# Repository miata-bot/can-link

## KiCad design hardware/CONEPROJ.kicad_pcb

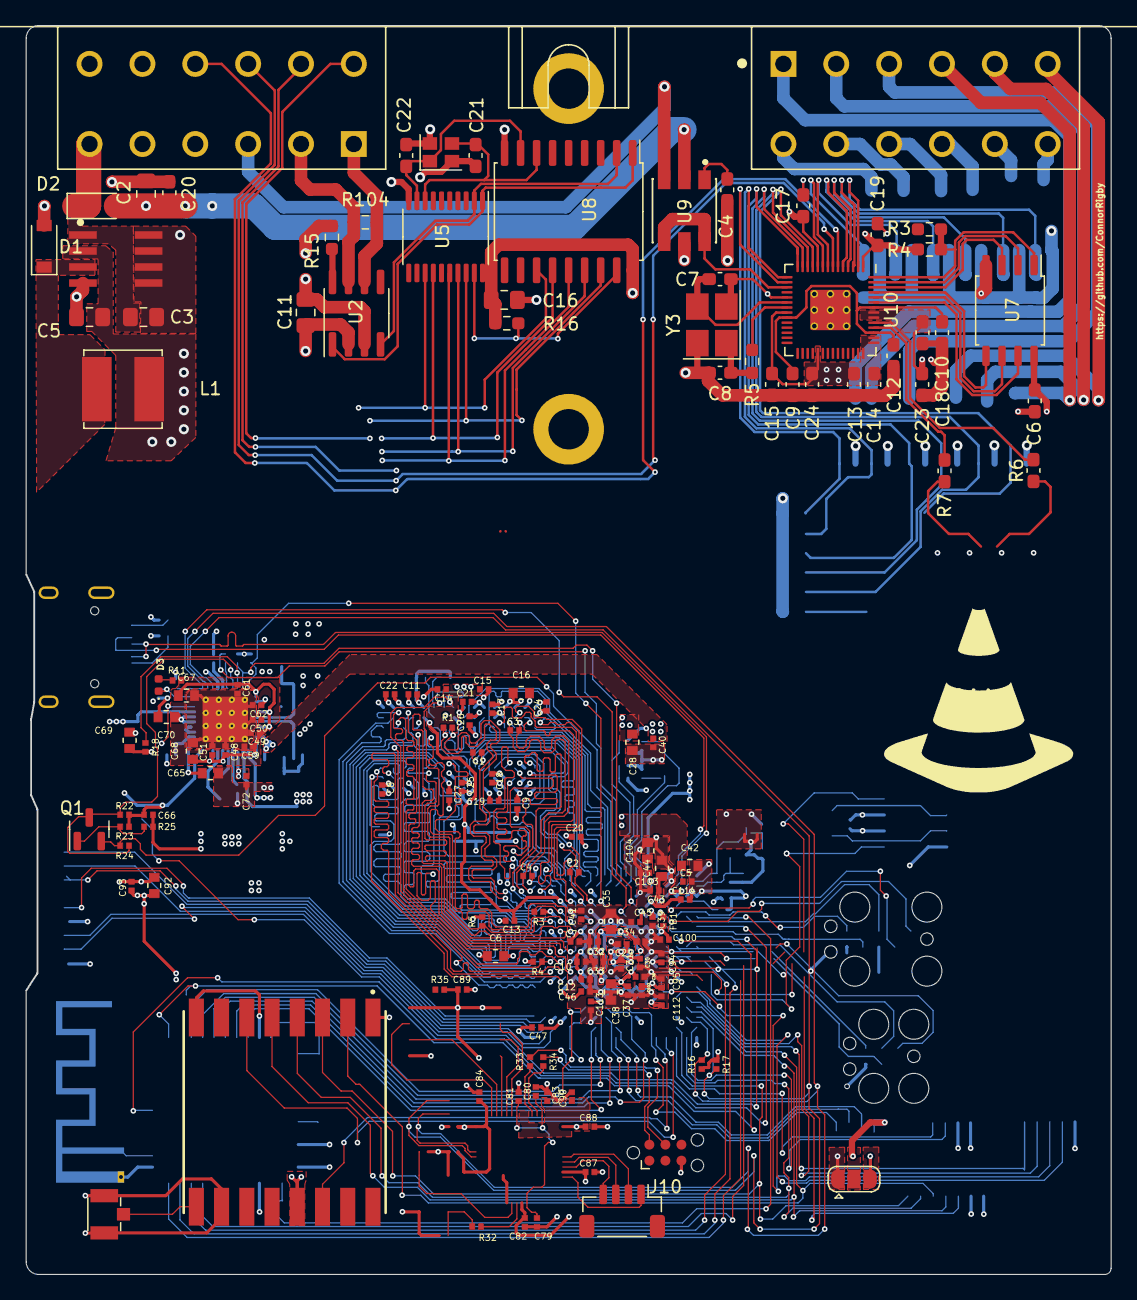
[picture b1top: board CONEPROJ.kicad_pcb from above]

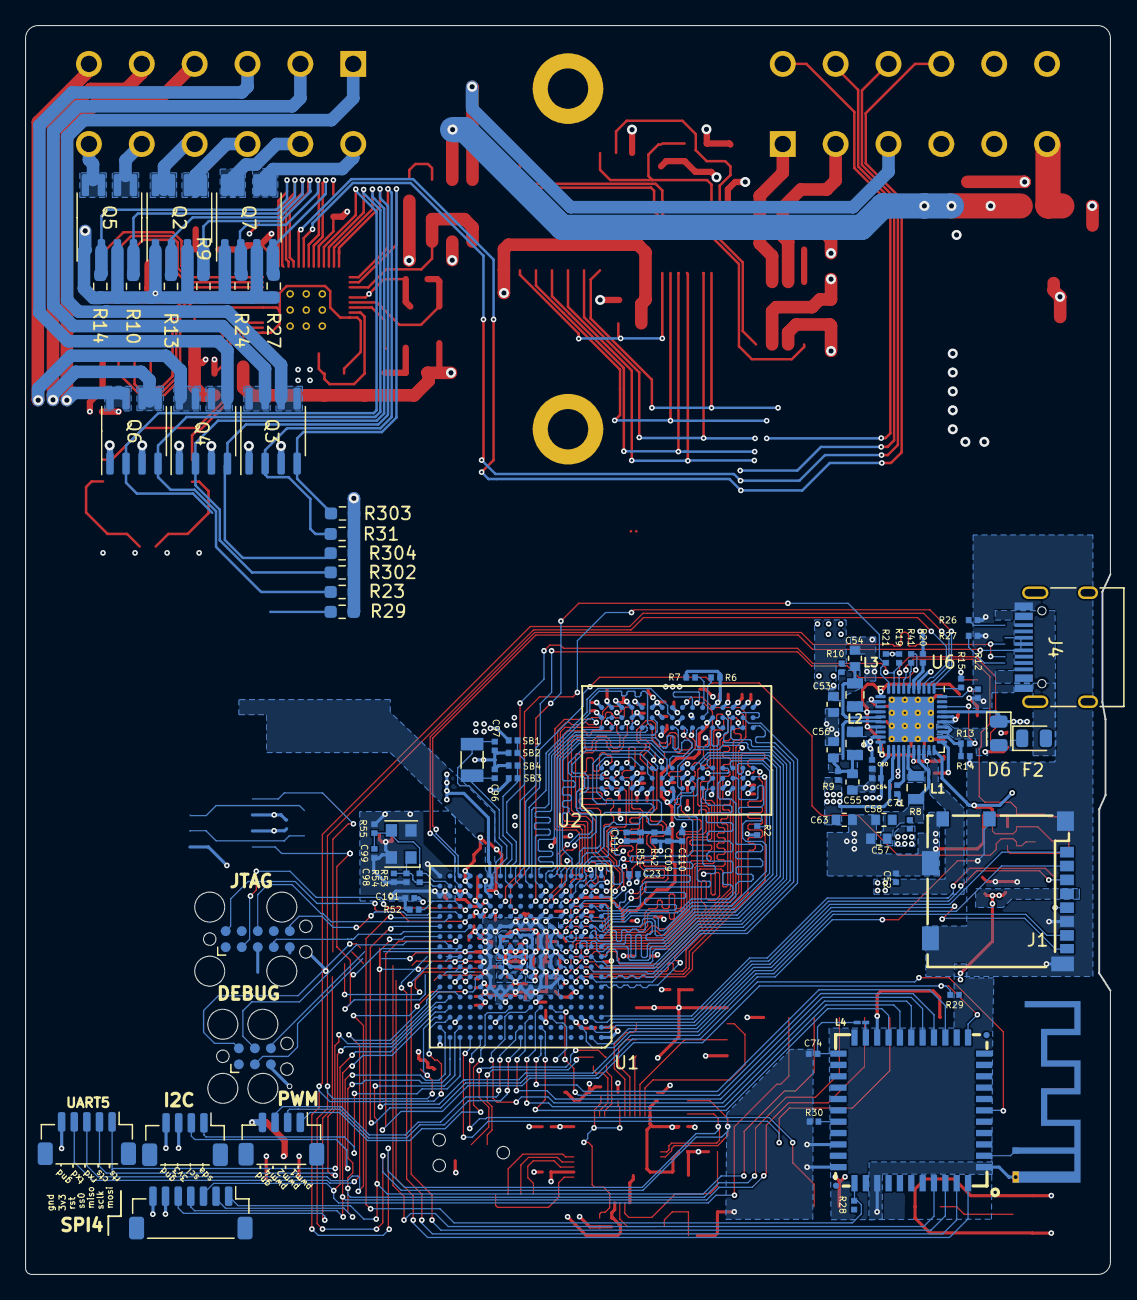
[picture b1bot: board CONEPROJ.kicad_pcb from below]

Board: 4 copper layers, 86.0 x 99.0 mm, 240 parts (89 on the bottom side), 60 nets.

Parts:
AE1: U.FL-R-SMT-1(10); HRS_U.FL-R-SMT-1(10)
ANT1: PCB_ANTENNA; Texas_SWRA117D_2.4GHz_Left
C1, C2#2, C3, C4#2: 2.2pF; C_0402_narrow
C2, C3#2, C5#2, C11, C16: 10uF; C_0805_2012Metric_Pad1.18x1.45mm_HandSolder
C4, C10, C13, C14, C15, C17#2, C18, C19#2, C20#2, C23, C24#2: 0.1uF; C_0603_1608Metric_Pad1.08x0.95mm_HandSolder
C5, C7#2, C8#2, C9#2, C10#2, C11#2, C12, C13#2, C14#2, C15#2, C17, C18#2, C19, C20, C21#2, C22, C23#2, C24, C25, C26, C27, C30, C31, C32, C33, C34, C36, C37, C40, C41, C43, C45, C46, C47, C94, C95, C102, C114: 0.22uF; C_0402_narrow
C6, C42, C44, C53, C54, C55, C56, C57, C58, C104: 10uF; C_0603_narrow
C6#2, C9, C12#2: 1uF; C_0603_1608Metric_Pad1.08x0.95mm_HandSolder
C7, C8: 10pF; C_0603_1608Metric_Pad1.08x0.95mm_HandSolder
C16#2, C28, C35, C38, C92: 22uF; C_0603_narrow
C21, C22#2: 22pf; C_0603_1608Metric_Pad1.08x0.95mm_HandSolder
C29, C39, C48, C49, C50, C52, C60, C62, C110: 4.7uF; C_0402_narrow
C51, C59, C61, C64, C71, C72, C79, C81, C89, C101: 1uF; C_0402_narrow
C63: 1uF; C_0603_narrow
C65: 0.1uF; C_0603_narrow
C66: 0.47uF; C_0402_narrow
C67, C68: 100uF; C_0603_narrow
C69, C70: 4.7uF; C_0603_narrow
C74: 4.7F; C_0402_narrow
C80, C82, C83, C84, C87, C88, C90, C93, C100, C103, C109, C111, C112, C113: 0.1uF; C_0402_narrow
C96, C97, C98, C99: 18pF; C_0402_narrow
D1, D2: D_Small; D_SOD-123
D3: LED; LED_0402_1005Metric
D6: D_Schottky; D_0805_2012Metric
F2: Polyfuse; D_0805_2012Metric
FB1: Bead; R_0402_narrow
H302, H304: MountingHole_Pad; MountingHole_3.2mm_M3_DIN965_Pad
J1: SD-104031; uSD_104031
J2: TAG_CONNECT_JTAG; Tag-Connect_TC2050-IDC-FP_2x05_P1.27mm_Vertical
J3: TC2030-IDC; Tag-Connect_TC2030-IDC-FP_2x03_P1.27mm_Vertical
J4: DTM1312PA12PBR008; TE_DTM1312PA12PBR008
J4#2: USB_C_Receptacle_USB2.0; USB_C_Receptacle_HRO_TYPE-C-31-M-12
J6: UART5; JST_SH_BM05B-SRSS-TB_1x05-1MP_P1.00mm_Vertical
J7: I2C4; JST_SH_BM04B-SRSS-TB_1x04-1MP_P1.00mm_Vertical
J8: ECSPI4; JST_SH_BM07B-SRSS-TB_1x07-1MP_P1.00mm_Vertical
J9: PWM; JST_SH_BM04B-SRSS-TB_1x04-1MP_P1.00mm_Vertical
J10: TC2030-IDC; Tag-Connect_TC2030-IDC-NL_2x03_P1.27mm_Vertical
J11: Conn_01x05; JST_SH_BM04B-SRSS-TB_1x04-1MP_P1.00mm_Vertical
JP1: IO_SW; SolderJumper-3_P1.3mm_Open_RoundedPad1.0x1.5mm
L1: 6.8uH; L_Bourns_SRN6045TA
L1#2, L2, L3: 1uH; L_0805_narrow
L4: 3.3uH; L_01005_0402Metric_Pad0.57x0.30mm_HandSolder
MOD1: RTL8723BS; RL-SM02BD(RTL8723BS)
Q1: 2SK3018; SOT-23
Q2, Q3, Q4, Q5, Q6, Q7: Q_Dual_NMOS_S1G1S2G2D2D2D1D1; SO-8_3.9x4.9mm_P1.27mm
R1: 470; R_0402_narrow
R2, R4, R5#2: 10K; R_0402_narrow
R3, R5, R15: 1k; R_0603_1608Metric_Pad0.98x0.95mm_HandSolder
R3#2, R6#2, R7#2: 240; R_0402_narrow
R4#2: 10k,DNF; R_0603_1608Metric_Pad0.98x0.95mm_HandSolder
R6, R7: 27.4; C_0603_1608Metric_Pad1.08x0.95mm_HandSolder
R8, R9, R10: 0.02; R_0402_narrow
R9#2, R10#2, R13#2, R14#2, R23#2, R24#2, R27, R29, R31, R302, R303, R304: 100k; R_0603_1608Metric_Pad0.98x0.95mm_HandSolder
R11: 47; R_0402_narrow
R12, R14, R24: DNP; R_0402_narrow
R13, R16, R17, R52: 4.7K; R_0402_narrow
R15#2, R18, R19, R21, R22, R23, R25: 100K; R_0402_narrow
R16#2: 10k; R_0603_1608Metric_Pad0.98x0.95mm_HandSolder
R20, R41: 0R; R_0402_narrow
R26, R27#2: 5.1k; R_0402_narrow
R28, R29#2, R32, R35: 1k; R_0402_narrow
R30: 7.13; R_0402_narrow
R33, R34: 27.4; R_0402_narrow
R42, R51: 1.5K; R_0402_narrow
R53: 1M; R_0402_narrow
R54: 499; R_0402_narrow
R55: 2.2M; R_0402_narrow
R104: 120, DNP; R_0603_1608Metric_Pad0.98x0.95mm_HandSolder
SB1, SB2, SB3, SB4: 4.7K; R_0402_narrow
U1: IMX6UL_BGA289
U2: SN65HVD230; SOIC-8_3.9x4.9mm_P1.27mm
U2#2: DDR3_BGA96
U5: MCP2515-xST; TSSOP-20_4.4x6.5mm_P0.65mm
U5#2: RFM69HCW; XCVR_RFM69HW
U6: PF1550; QFN-40-1EP_5x5mm_P0.4mm_EP3.6x3.6mm_ThermalVias
U7: W25Q128JVS; SOIC-8_5.23x5.23mm_P1.27mm
U8: MCP2515-xSO; SOIC-18W_7.5x11.6mm_P1.27mm
U9: WS2815B; worldsemi-WS2815B-MFG
U10: RP2040; RP2040-QFN-56
U304: AP1509; SO08
XTAL2: 24MHz 50ppm; Oscillator_SMD_EuroQuartz_XO32-4Pin_3.2x2.5mm
Y1: 32.768 kHz; Crystal_SMD_3215-2Pin_3.2x1.5mm
Y2: 16mhz; Crystal_SMD_2520-4Pin_2.5x2.0mm
Y3: 12mhz; Crystal_SMD_3225-4Pin_3.2x2.5mm_HandSoldering

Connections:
+1V1: C9.1, C10.1, C12#2.1, U10.23 (DVDD), U10.45 (VREG_VOUT), U10.50 (DVDD)
+3V3: C6#2.1, C11.1, C13.1, C14.1, C15.1, C16.1, C17#2.1, C18.1, C19#2.1, C23.1, C24#2.1, R4#2.2, R16#2.1, U2.3 (VCC), U5.20 (VDD), U7.8 (VCC), U8.18 (VDD), U10.1 (IOVDD), U10.10 (IOVDD), U10.22 (IOVDD), U10.33 (IOVDD), U10.42 (IOVDD), U10.43 (ADC_AVDD), U10.44 (VREG_IN), U10.48 (USB_VDD), U10.49 (IOVDD)
+5V: C5#2.1, L1.2, U304.2 (VOUT)
/B_OUT: J4.A12, Q7.5 (D), Q7.6 (D)
/CANH: J4.B2, R104.2, U2.7 (CANH)
/CANL: J4.B1, R104.1, U2.6 (CANL)
/CAN_RX: U2.4 (R), U5.2 (RXCAN), U8.2 (RXCAN)
/CAN_TX: U2.1 (D), U5.1 (TXCAN), U8.1 (TXCAN)
/GPO_1: Q3.4 (G), R303.1, U10.16 (GPIO13)
/GPO_1_OUT: J4.A1, Q3.5 (D), Q3.6 (D)
/GPO_2: Q3.2 (G), R31.1, U10.15 (GPIO12)
/GPO_2_OUT: J4.A2, Q3.7 (D), Q3.8 (D)
/GPO_3: Q4.4 (G), R304.1, U10.14 (GPIO11)
/GPO_3_OUT: J4.A3, Q4.5 (D), Q4.6 (D)
/GPO_4: Q6.2 (G), R29.1, U10.11 (GPIO8)
/GPO_4_OUT: J4.A4, Q6.7 (D), Q6.8 (D)
/GPO_5: Q6.4 (G), R23#2.1, U10.12 (GPIO9)
/GPO_5_OUT: J4.A5, Q6.5 (D), Q6.6 (D)
/GPO_6: Q4.2 (G), R302.1, U10.13 (GPIO10)
/GPO_6_OUT: J4.A6, Q4.7 (D), Q4.8 (D)
/GPO_7: Q5.2 (G), R14#2.1, U10.2 (GPIO0)
/GPO_7_OUT: J4.A7, Q5.7 (D), Q5.8 (D)
/GPO_8: Q5.4 (G), R10#2.1, U10.3 (GPIO1)
/GPO_8_OUT: J4.A8, Q5.5 (D), Q5.6 (D)
/GPO_9: Q2.2 (G), R13#2.1, U10.4 (GPIO2)
/GPO_9_OUT: J4.A9, Q2.7 (D), Q2.8 (D)
/G_OUT: J4.A11, Q7.7 (D), Q7.8 (D)
/I2C1_SCL: J4.B10, U10.7 (GPIO5)
/I2C1_SDA: J4.B9, U10.6 (GPIO4)
/LEDA: U9.4 (DIN), U9.6 (BIN), U10.17 (GPIO14)
/LEDA_OUT: J4.B3, U9.3 (DO)
/LEDB: Q7.4 (G), R27.1, U10.9 (GPIO7)
/LEDG: Q7.2 (G), R24#2.1, U10.8 (GPIO6)
/LEDR: Q2.4 (G), R9#2.1, U10.5 (GPIO3)
/MCP_INT: U5.13 (~INT), U8.12 (~INT)
/MCP_OSC1: C22#2.2, U5.9 (OSC1), U8.8 (OSC1), Y2.1
/MCP_OSC2: C21.1, U5.8 (OSC2), U8.7 (OSC2), Y2.3
/MCP_RESET: R16#2.2, U5.19 (~RESET), U8.17 (~RESET)
/QSPI_SCLK: U7.6 (CLK), U10.52 (QSPI_SCLK)
/QSPI_SD0: U7.5 (DI(IO0)), U10.53 (QSPI_SD0)
/QSPI_SD1: U7.2 (DO(IO1)), U10.55 (QSPI_SD1)
/QSPI_SD2: U7.3 (IO2), U10.54 (QSPI_SD2)
/QSPI_SD3: U7.7 (IO3), U10.51 (QSPI_SD3)
/QSPI_SS: R3.2, R4#2.1, U7.1 (~CS), U10.56 (QSPI_SS)
/R_OUT: J4.A10, Q2.5 (D), Q2.6 (D)
/SPI0_CE0_N: U5.18 (~CS), U8.16 (~CS)
/SPI0_MISO: U5.17 (SO), U8.15 (SO)
/SPI0_MOSI: U5.16 (SI), U8.14 (SI)
/SPI0_SCLK: U5.14 (SCK), U8.13 (SCK)
/VIN: C3#2.1, D2.1 (K), J4.B6, U304.1 (VIN)
GND: AE1.1, AE1.3, ANT1.2 (Shield), C2.2, C3#2.2, C4.2, C5.2, C5#2.2, C6.2, C6#2.2, C7.2, C7#2.2, C8.1, C8#2.2, C9.2, C9#2.2, C10.2, C10#2.2, C11.2, C11#2.2, C12.2, C12#2.2, C13.2, C13#2.2, C14.2, C14#2.2, C15.2, C15#2.2, C16.2, C16#2.2, C17.2, C17#2.2, C18.2, C18#2.2, C19.2, C19#2.2, C20.2, C20#2.2, C21.2, C21#2.2, C22.2, C22#2.1, C23.2, C23#2.2, C24.2, C24#2.2, C25.2, C26.2, C27.2, C28.2, C29.2, C30.2, C31.2, C32.2, C33.2, C34.2, C35.2, C36.2, C37.2, C38.2, C39.2, C40.2, C41.2, C42.2, C43.2, C44.2, C45.2, C46.2, C47.2, C48.2, C49.2, C50.2, C51.2, C52.2, C53.2, C54.2, C55.2, C56.2, C57.2, C58.2, C59.2, C60.2, C61.2, C62.2, C63.2, C64.2, C65.2, C66.2, C67.2, C68.2, C69.2, C70.2, C71.2, C72.2, C74.2, C79.2, C80.2, C81.2, C82.2, C83.1, C84.2, C87.2, C88.2, C89.2, C90.2, C92.2, C93.2, C94.2, C95.2, C96.2, C97.2, C98.2, C99.2, C100.2, C101.2, C102.2, C103.2, C104.2, C110.2, C111.2, C112.2, C113.2, C114.2, D1.2 (A), H302.1, H304.1, J1.6 (GND), J1.10 (SW2), J1.11 (Shield1), J1.12 (Shield2), J1.13 (Shield3), J1.14 (Shield4), J2.3 (GND), J2.5 (GND), J3.5, J4.B7, J4#2.A1 (GND), J4#2.A12 (GND), J4#2.B1 (GND), J4#2.B12 (GND), J6.5, J7.4, J8.7, J10.5 (GND), JP1.1 (A), MOD1.1, MOD1.20, MOD1.31, MOD1.33, MOD1.36, Q2.1 (S), Q2.3 (S), Q3.1 (S), Q3.3 (S), Q4.1 (S), Q4.3 (S), Q5.1 (S), Q5.3 (S), Q6.1 (S), Q6.3 (S), Q7.1 (S), Q7.3 (S), R2.2, R3#2.1, R4.2, R5#2.2, R6#2.1, R7#2.1, R9#2.2, R10#2.2, R12.2, R13#2.2, R14.1, R14#2.2, R15.2, R20.1, R23#2.2, R24#2.2, R25.1, R26.2, R27.2, R27#2.2, R29.2, R30.1, R31.2, R51.1, R52.1, R54.2, R55.2, R302.2, R303.2, R304.2, SB2.2, SB4.2, U1.A1 (VSS), U1.A17 (VSS), U1.C3 (VSS), U1.C7 (VSS), U1.C11 (VSS), U1.C15 (VSS), U1.E8 (VSS), U1.E11 (VSS), U1.F6 (VSS), U1.F7 (VSS), U1.F8 (VSS), U1.F9 (VSS), U1.F10 (VSS), U1.F11 (VSS), U1.F12 (VSS), U1.G3 (VSS), U1.G5 (VSS), U1.G7 (VSS), U1.G12 (VSS), U1.G15 (VSS), U1.H7 (VSS), U1.H12 (VSS), U1.J5 (VSS), U1.J7 (VSS), U1.J12 (VSS), U1.K7 (VSS), U1.K12 (VSS), U1.L3 (VSS), U1.L7 (VSS), U1.L12 (VSS), U1.M7 (VSS), U1.M8 (VSS), U1.M9 (VSS), U1.M10 (VSS), U1.M11 (VSS), U1.M12 (NGND_KEL0), U1.N3 (VSS), U1.N5 (VSS), U1.N7 (TEST_MODE), U1.R3 (VSS), U1.R5 (VSS), U1.R7 (VSS), U1.R11 (VSS), U1.R16 (VSS), U1.R17 (VSS), U1.T14 (VSS), U1.U1 (VSS), U1.U14 (VSS), U1.U17 (VSS), U2.2 (GND), U2#2.A9 (VSS), U2#2.B1 (VSSQ), U2#2.B3 (VSS), U2#2.B9 (VSSQ), U2#2.D1 (VSSQ), U2#2.D8 (VSSQ), U2#2.E1 (VSS), U2#2.E2 (VSSQ), U2#2.E8 (VSSQ), U2#2.F9 (VSSQ), U2#2.G1 (VSSQ), U2#2.G8 (VSS), U2#2.G9 (VSSQ), U2#2.J2 (VSS), U2#2.J8 (VSS), U2#2.M1 (VSS), U2#2.M9 (VSS), U2#2.P1 (VSS), U2#2.P9 (VSS), U2#2.T1 (VSS), U2#2.T9 (VSS), U5.10 (VSS), U5#2.1 (GND), U5#2.8 (GND), U5#2.10 (GND), U6.41 (EP), U7.4 (GND), U8.9 (VSS), U9.5 (GND), U10.19 (TESTEN), U10.57 (GND), U304.4 (SD), U304.5 (GND5), U304.6 (GND6), U304.7 (GND7), U304.8 (GND8), XTAL2.2, XTAL2.4, Y2.2, Y2.4, Y3.2, Y3.4
unnamed: C4.1, U9.1 (VCC)
unnamed: C7.1, U10.20 (XIN), Y3.3
unnamed: C8.2, R5.2, Y3.1
unnamed: D1.1 (K), L1.1, U304.3 (FB)
unnamed: R5.1, U10.21 (XOUT)
unnamed: R6.1, U10.47 (USB_DP)
unnamed: R7.2, U10.46 (USB_DM)
unnamed: R15.1, U2.8 (Rs)
VCC: C2.1, C20#2.1, D2.2 (A), U9.2 (VDD)

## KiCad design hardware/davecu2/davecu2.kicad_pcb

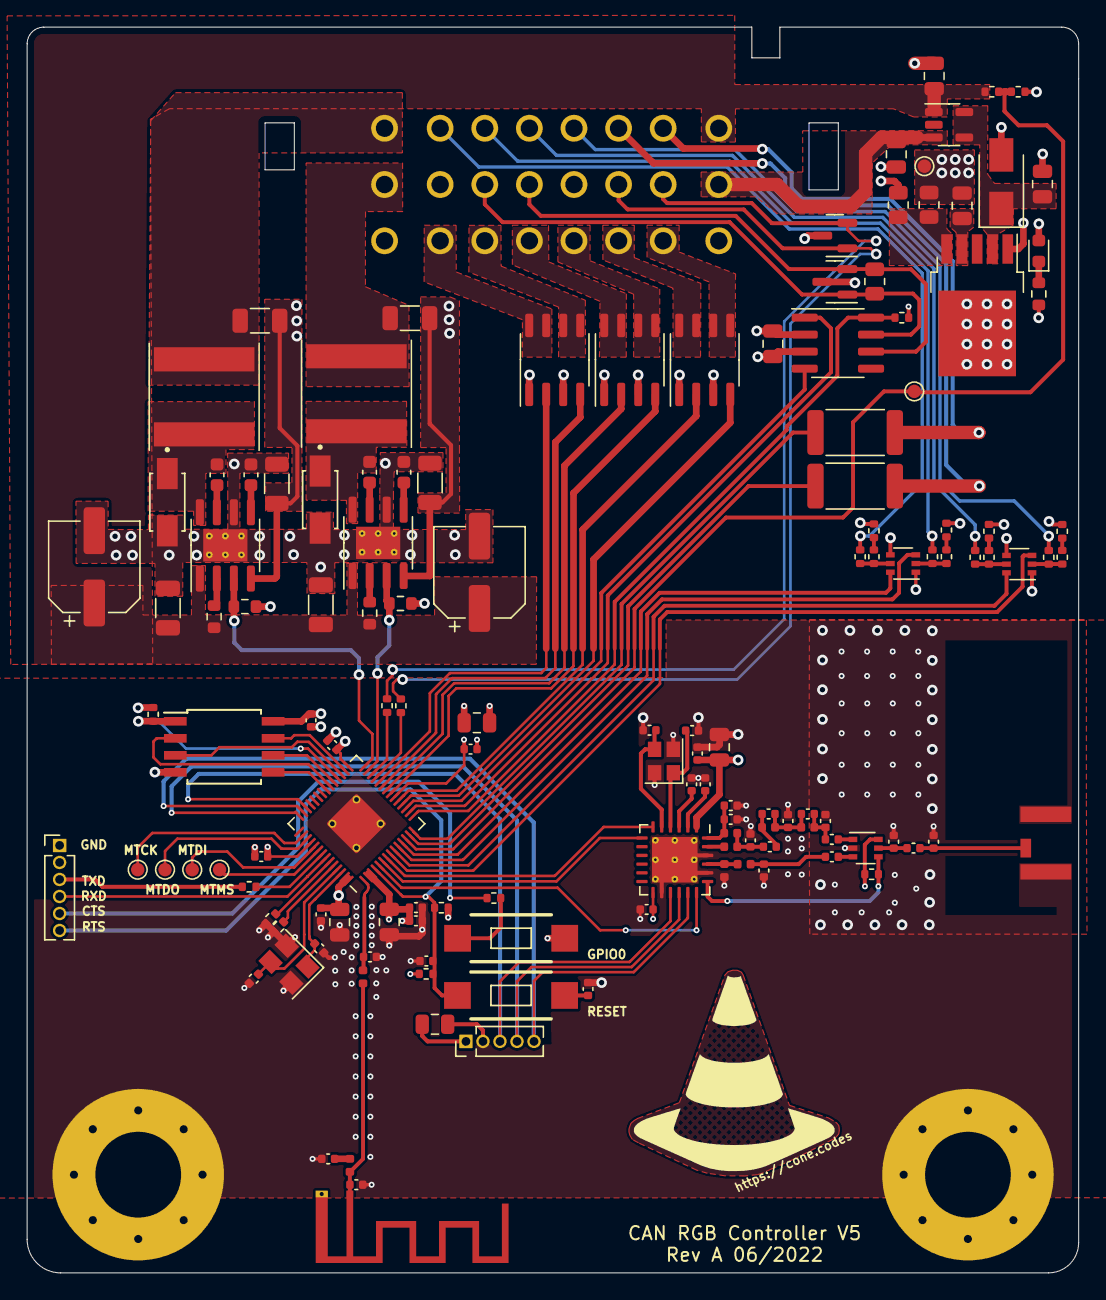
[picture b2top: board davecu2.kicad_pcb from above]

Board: 4 copper layers, 78.5 x 93.0 mm, 138 parts (0 on the bottom side), 112 nets.

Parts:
AE2: 7488910915
AE3: Antenna_Shield; Texas_SWRA117D_2.4GHz_Left
C2: 0.01uF; C_0402_1005Metric
C3, C4, C11: DNF; C_0402_1005Metric
C5, C6: 8.2pF; C_0402_1005Metric
C7: 6.8pF; C_0402_1005Metric
C8, C15: 5.6pF; C_0402_1005Metric
C9: 0.5pF; C_0402_1005Metric
C10: 1.2pF; C_0402_1005Metric
C12, C14: 100pF; C_0402_1005Metric
C13: 5.6nH; L_0402_1005Metric
C16: C_Small; C_0402_1005Metric
C17, C26, C28, C30, C41, C43, C44, C45: 10uF; C_0805_2012Metric
C18, C19, C20, C21, C24, C27, C31, C32, C33: 0.1uF; C_0402_1005Metric
C22, C23, C38, C39: 16pF; C_0402_1005Metric
C25, C29, C37, C56: 1uF; C_0402_1005Metric
C34: 4.6pF; C_0402_1005Metric
C35: 4pF; C_0402_1005Metric
C36: 2pF; C_0402_1005Metric
C40, C42: 1uF; C_0805_2012Metric
C46, C47: C_Small; CP_Elec_6.3x7.7
C48, C49: 4.7uF X5R; C_1206_3216Metric
C50, C51: 0.1uF; C_0603_1608Metric
C52, C53: C_Small; C_0603_1608Metric
C54, C55: 0.68μF; C_1206_3216Metric
D2: GRN; LED_0603_1608Metric
D3: RB496EA; SOT-23-5
D4: D_Schottky_Small; D_SMA
D5: PESD2USB3UV-T; SOT-23
D6: PESD2CANFD24V-T; SOT-23
D7, D8: B250A-13-F; DIOM5226X240N
H2, H3: MountingHole_Pad; MountingHole_6.4mm_M6_Pad_Via
J2: CONSOLE; PinHeader_1x06_P1.27mm_Vertical
J3: Delphi_Sicma_24; Delphi_Sicma_24_Black
J4: Conn_01x05; PinHeader_1x05_P1.27mm_Vertical
L2: 22nH; L_0402_1005Metric
L3: 3.9nH; L_0402_1005Metric
L4, L5: 5.6nH; L_0402_1005Metric
L6: 120nH; L_0402_1005Metric
L7: 2nH; L_0402_1005Metric
L8: 2.2nH; L_0402_1005Metric
L9, L10: NR8040T100M; L_Taiyo-Yuden_NR-80xx
Q2, Q3, Q4: STS8DNF3LL; SO-8_3.9x4.9mm_P1.27mm
Q5, Q6: MBT3904DW1T1G; SOT-363_SC-70-6
R2, R5, R6: 0R; R_0402_1005Metric
R3, R8, R9, R10, R11, R12, R17, R18, R29, R38: 10k; R_0402_1005Metric
R4, R15, R16, R21, R22: 499R; R_0402_1005Metric
R7: 100k; R_0402_1005Metric
R13, R14, R19, R20, R31: 1k; R_0402_1005Metric
R23, R24: 0R; R_2512_6332Metric
R25: 240R; R_0603_1608Metric
R26: 56.7k; R_0805_2012Metric
R27: 10k; R_0805_2012Metric
R28: 36k; R_0402_1005Metric
R30: 120,DNF; R_0805_2012Metric
R32, R33, R34, R35: R_Small; R_0603_1608Metric
R36, R37: R_Small; R_1206_3216Metric
SW2, SW3: SW_Push; SW_RS-032G05A3-SMRT
TP2: 3V3OUT; TestPoint_Pad_D1.0mm
TP3: VSENSE; TestPoint_Pad_D1.0mm
TP4: MTCK; TestPoint_Pad_D1.0mm
TP5: MTDO; TestPoint_Pad_D1.0mm
TP6: MTDI; TestPoint_Pad_D1.0mm
TP7: MTMS; TestPoint_Pad_D1.0mm
U2: PE42421SCAA-Z; SOT-363_SC-70-6
U3: SX1231HIMLTRT; QFN-24-1EP_5x5mm_P0.65mm_EP3.4x3.4mm_ThermalVias
U4: ESP32-S3R2; QFN-56
U5: W25Q128JVS; SOIC-8W_5.3x5.3mm_P1.27mm
U6, U7: A6213-1; SOIC-8-1EP_3.9x4.9mm_P1.27mm_EP2.41x3.3mm_ThermalVias
U8: BD33C0AWFP-CE2; TO-252-5_TabPin6
U9: SN65HVD230; SOIC-8_3.9x4.9mm_P1.27mm
Y2: 32mhz; Crystal_SMD_2520-4Pin_2.5x2.0mm
Y3: 40MHZ; Crystal_SMD_3225-4Pin_3.2x2.5mm

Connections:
+3V3: C17.1, C18.1, C19.1, C24.1, C25.1, C26.1, C27.1, C28.1, C29.1, C30.1, C31.1, C32.1, C33.1, C40.2, C44.1, C45.2, D2.2 (A), J4.1, R2.2, R3.2, R7.1, R26.2, R38.2, TP2.1, U2.6 (V2), U3.1 (VBAT1), U3.13 (VBAT2), U4.2 (VDD3P3), U4.3 (VDD3P3), U4.20 (VDD3P3_RTC), U4.29 (VDD_SPI), U4.46 (VDD3P3_CPU), U4.55 (VDDA1), U4.56 (VDDA2), U5.8 (VCC), U9.3 (VCC)
/CAN_EN: R31.1, U4.15 (GPIO10), U9.8 (Rs)
/CAN_H: D6.1 (A1), J3.B3, R30.2, U9.7 (CANH)
/CAN_L: D6.2 (A2), J3.B4, R30.1, U9.6 (CANL)
/CS1: U3.18 (NSS), U4.5 (GPIO0)
/Connectors/DI_1: J3.C2, R18.1
/Connectors/DI_2: J3.C3, R11.1
/Connectors/DI_3: J3.C4, R17.1
/Connectors/DI_4: J3.C5, R12.1
/Connectors/IGNITION: J3.A1, U8.1 (CTRL)
/Connectors/PIXEL_1: J3.C7, R23.2
/Connectors/PIXEL_2: J3.C6, R24.2
/Connectors/RGB1_12V: C54.1, J3.C1, L9.2
/Connectors/RGB1_B: J3.A4, Q3.7 (D), Q3.8 (D)
/Connectors/RGB1_G: J3.A3, Q2.5 (D), Q2.6 (D)
/Connectors/RGB1_R: J3.A2, Q2.7 (D), Q2.8 (D)
/Connectors/RGB2_12V: C55.1, J3.B1, L10.2
/Connectors/RGB2_B: J3.A7, Q4.5 (D), Q4.6 (D)
/Connectors/RGB2_G: J3.A6, Q4.7 (D), Q4.8 (D)
/Connectors/RGB2_R: J3.A5, Q3.5 (D), Q3.6 (D)
/Connectors/USB_D_N: D5.1 (K), J3.B6, R5.2
/Connectors/USB_D_P: D5.2 (K), J3.B7, R6.2
/Connectors/USB_VBUS: C43.1, D3.3 (A), J3.B8
/Connectors/VBATT: C41.2, C46.1, C47.1, C48.2, C49.2, D3.1 (A), J3.C8, R28.1, R34.1, R35.1, U6.1 (VIN), U7.1 (VIN)
/ESP32-S3/CHIP_PU: C56.1, J2.6, R3.1, R38.1, SW2.1, U4.4 (CHIP_PU)
/ESP32-S3/CTS: J2.5, R8.1
/ESP32-S3/GPIO0_BOOTSTRAP: R8.2, SW3.1
/ESP32-S3/GPIO3: Q6.3 (C2), U4.8 (GPIO3)
/ESP32-S3/GPIO4: Q6.6 (C1), U4.9 (GPIO4)
/ESP32-S3/GPIO5: Q5.3 (C2), U4.10 (GPIO5)
/ESP32-S3/GPIO6: Q5.6 (C1), U4.11 (GPIO6)
/ESP32-S3/GPIO8: R24.1, U4.13 (GPIO8)
/ESP32-S3/GPIO9: R23.1, U4.14 (GPIO9)
/ESP32-S3/GPIO13: Q4.4 (G), U4.18 (GPIO13)
/ESP32-S3/GPIO14: Q4.2 (G), U4.19 (GPIO14)
/ESP32-S3/GPIO17: Q2.4 (G), U4.23 (GPIO17)
/ESP32-S3/GPIO19: R5.1, U4.25 (GPIO19)
/ESP32-S3/GPIO20: R6.1, U4.26 (GPIO20)
/ESP32-S3/GPIO21: R33.2, U4.27 (GPIO21), U6.3 (EN)
/ESP32-S3/GPIO45: R9.1, U4.51 (GPIO45)
/ESP32-S3/GPIO46: R10.1, U4.52 (GPIO46)
/ESP32-S3/GPIO_18: Q2.2 (G), U4.24 (GPIO18)
/ESP32-S3/LNA_IN: C34.2, L7.1, U4.1 (LNA_IN)
/ESP32-S3/MTCK: TP4.1, U4.44 (MTCK)
/ESP32-S3/MTDI: TP6.1, U4.47 (MTDI)
/ESP32-S3/MTDO: TP5.1, U4.45 (MTDO)
/ESP32-S3/MTMS: TP7.1, U4.48 (MTMS)
/ESP32-S3/RF_ANT: AE3.1 (A), C35.2, L7.2, L8.1
/ESP32-S3/RTC_XTAL_N: Q3.2 (G), U4.22 (XTAL_32K_N)
/ESP32-S3/RTC_XTAL_P: Q3.4 (G), U4.21 (XTAL_32K_P)
/ESP32-S3/SPICLK: U4.33 (SPICLK), U5.6 (CLK)
/ESP32-S3/SPICS0: R7.2, U4.32 (SPICS0), U5.1 (~CS)
/ESP32-S3/SPID: U4.35 (SPID), U5.5 (DI(IO0))
/ESP32-S3/SPIHD: U4.30 (SPIHD), U5.7 (IO3)
/ESP32-S3/SPIQ: U4.34 (SPIQ), U5.2 (DO(IO1))
/ESP32-S3/SPIWP: U4.31 (SPIWP), U5.3 (IO2)
/ESP32-S3/U0RXD: J2.4, U4.50 (U0RXD)
/ESP32-S3/U0TXD: J2.3, R4.1
/ESP32-S3/XTAL_N: C39.1, U4.53 (XTAL_N), Y3.3
/ESP32-S3/XTAL_P: C38.1, U4.54 (XTAL_P), Y3.1
/External-IO/PWMI1: R32.2, U4.28 (SPICS1), U7.3 (EN)
/External-IO/RGB1_BOOT: C52.1, U7.7 (BOOT)
/External-IO/RGB1_CS: C54.2, Q2.1 (S), Q2.3 (S), Q3.1 (S), R36.1, U7.4 (CS)
/External-IO/RGB1_SW: C52.2, D7.1 (K), L9.1, U7.8 (SW)
/External-IO/RGB1_VCC: C50.1, U7.5 (VCC)
/External-IO/RGB2_BOOT: C53.1, U6.7 (BOOT)
/External-IO/RGB2_CS: C55.2, Q3.3 (S), Q4.1 (S), Q4.3 (S), R37.1, U6.4 (CS)
/External-IO/RGB2_SW: C53.2, D8.1 (K), L10.1, U6.8 (SW)
/External-IO/RGB2_VCC: C51.1, U6.5 (VCC)
/GPIO_CAN_N: U4.17 (GPIO12), U9.4 (R)
/GPIO_CAN_P: U4.16 (GPIO11), U9.1 (D)
/MISO: J4.4, U3.16 (MISO), U4.42 (GPIO37)
/MOSI: J4.5, U3.17 (MOSI), U4.41 (GPIO36)
/Power/VCC: C42.2, D3.4 (K), D3.5 (K), D4.1 (K), U8.2 (VCC)
/SCLK: J4.3, U3.15 (SCK), U4.40 (GPIO35)
/SX1231/CER_ANT: AE2.3 (FEED), C9.2, C11.2
/SX1231/DIO0: U3.7 (DIO0), U4.6 (GPIO1)
/SX1231/NRESET: U3.6 (RESET), U4.7 (GPIO2)
/SX1231/PA_BOOST: L3.1, U3.23 (PA_BOOST)
/SX1231/RADIO_XTAL_N: C23.1, U3.5 (XTB), Y2.3
/SX1231/RADIO_XTAL_P: C22.1, U3.4 (XTA), Y2.1
/SX1231/RF1: C12.2, U2.1 (J3)
/SX1231/RF2: C14.2, U2.3 (J2)
/SX1231/RFC: C9.1, C10.2, U2.5 (J1)
/SX1231/RFIO: C13.1, L6.1, U3.21 (RFIO)
/SX1231/RX_TX: R2.1, U2.4 (V1), U3.19 (RXTX)
/SX1231/VR_ANA: C21.1, U3.2 (VR_ANA)
/SX1231/VR_DIG: C20.1, U3.3 (VR_DIG)
/SX1231/VR_PA: C2.1, C16.1, L2.1, U3.24 (VR_PA)
/VSENSE: R28.2, R29.1, TP3.1, U4.12 (GPIO7)
GND: AE2.1 (PCB_Trace), AE2.2 (PCB_Trace), AE3.2 (Shield), C2.2, C6.2, C7.2, C8.2, C10.1, C11.1, C15.2, C16.2, C17.2, C18.2, C19.2, C20.2, C21.2, C22.2, C23.2, C24.2, C25.2, C26.2, C27.2, C28.2, C29.2, C30.2, C31.2, C32.2, C33.2, C34.1, C35.1, C36.1, C37.2, C38.2, C39.2, C41.1, C42.1, C43.2, C44.2, C45.1, C46.2, C47.2, C48.1, C49.1, C50.2, C51.2, C56.2, D4.2 (A), D5.3 (A), D6.3 (common), D7.2 (A), D8.2 (A), H2.1, H3.1, J2.1, J3.A8, J3.B2, J3.B5, J4.2, L6.2, Q5.1 (E1), Q5.4 (E2), Q6.1 (E1), Q6.4 (E2), R9.2, R10.2, R15.2, R16.2, R21.2, R22.2, R25.2, R27.2, R29.2, R31.2, R32.1, R33.1, R36.2, R37.2, SW3.2, U2.2 (GND), U3.14 (GND), U3.20 (GND), U3.22 (GND), U3.25 (EP), U4.57 (GND), U5.4 (GND), U6.6 (GND), U6.9 (EP), U7.6 (GND), U7.9 (EP), U8.6 (GND), U9.2 (GND), Y2.2, Y2.4, Y3.2, Y3.4
unnamed: C3.1, C4.2, C7.1, L4.2, L5.1
unnamed: C3.2, C5.2, L4.1
unnamed: C5.1, C6.1, L2.2, L3.2
unnamed: C4.1, C8.1, C12.1, L5.2
unnamed: C13.2, C14.1, C15.1
unnamed: C36.2, L8.2
unnamed: C37.1, SW2.2
unnamed: C40.1, U8.4 (VO)
unnamed: D2.1 (K), R25.1
unnamed: Q5.2 (B1), R11.2, R13.1
unnamed: Q5.5 (B2), R18.2, R19.1
unnamed: Q6.2 (B1), R12.2, R14.1
unnamed: Q6.5 (B2), R17.2, R20.1
unnamed: R4.2, U4.49 (U0TXD)
unnamed: R13.2, R15.1
unnamed: R14.2, R16.1
unnamed: R19.2, R21.1
unnamed: R20.2, R22.1
unnamed: R26.1, R27.1, U8.5 (ADJ)
unnamed: R34.2, U6.2 (TON)
unnamed: R35.2, U7.2 (TON)

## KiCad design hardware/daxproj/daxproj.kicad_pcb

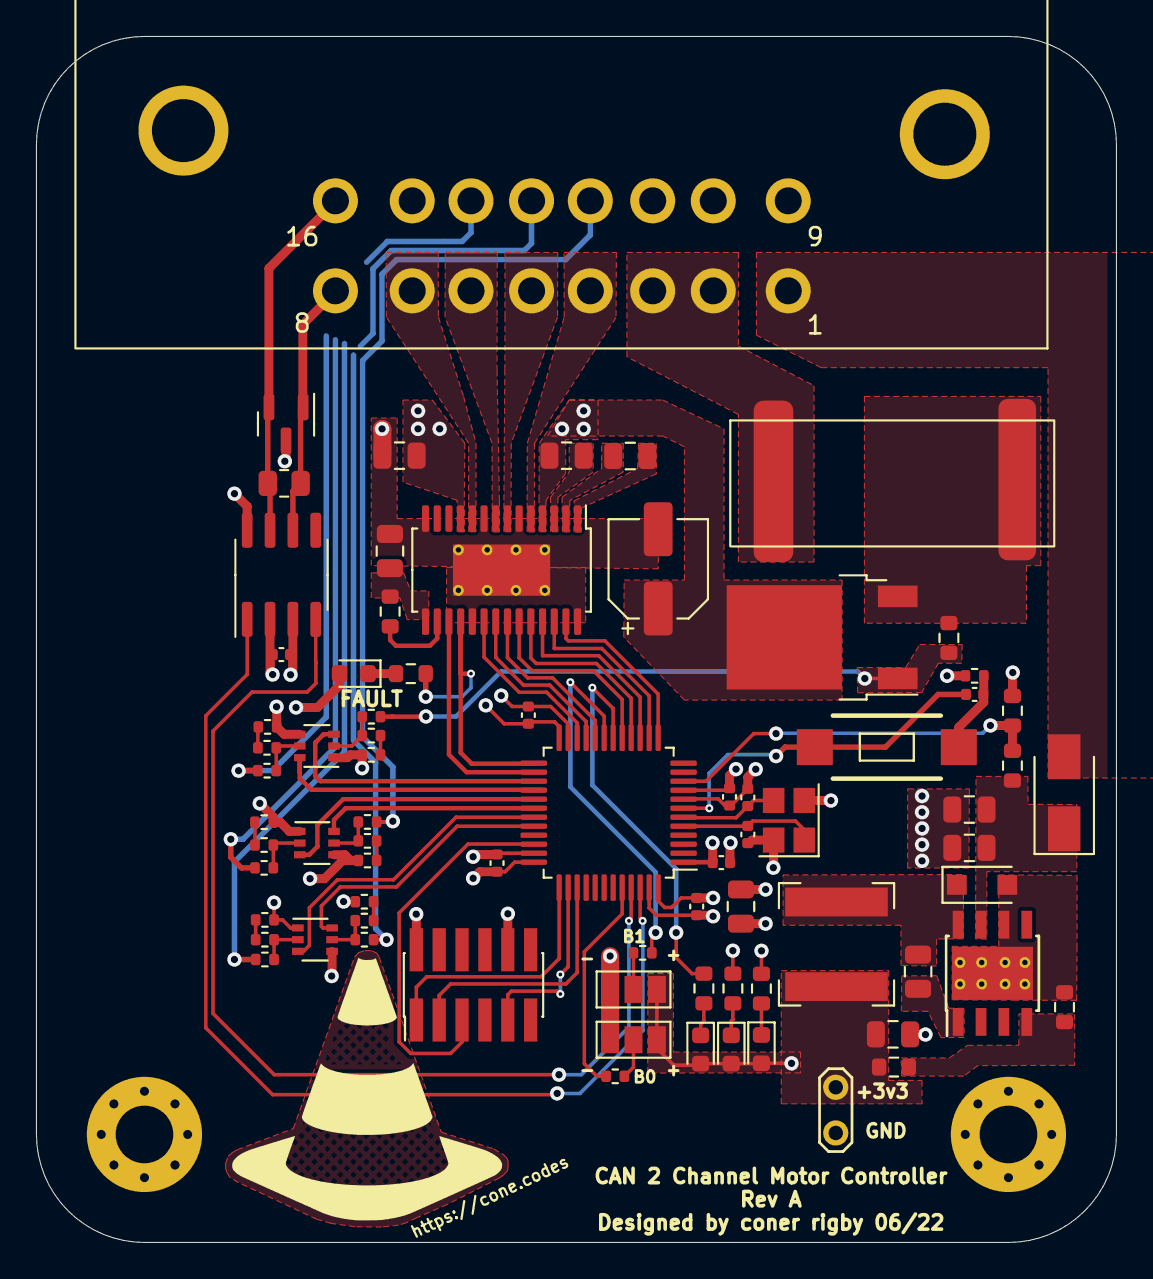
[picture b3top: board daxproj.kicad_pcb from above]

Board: 4 copper layers, 60.0 x 67.0 mm, 77 parts (0 on the bottom side), 71 nets.

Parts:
C1: 10uf; C_0805_2012Metric
C2: 1uf; C_0805_2012Metric
C3, C4: C_Small; C_0805_2012Metric
C5, C7, C8, C9, C10, C11, C18: 100nf; C_0402_1005Metric
C6: 4.7nf; C_0805_2012Metric
C12, C13: C_Small; C_0402_1005Metric
C14: 0.01uF; C_0805_2012Metric
C15: 0.1uF; C_0805_2012Metric
C16: 10uF; C_0805_2012Metric
C17: 10uF; CP_Elec_5x5.3
C19: 0.47uF; C_0805_2012Metric
D1: TPSMA6L78A; D_SMA
D2: D_Small; D_SOD-123F
D3, D4, D5: GRN; LED_0603_1608Metric
D6: RED; LED_0603_1608Metric
D7: PESD2CANFD24V-T; SOT-23
F1: Fuse; Keystone-3587-10TR
H1, H2: MountingHole_Pad; MountingHole_3.2mm_M3_Pad_Via
J2: Conn_02x08_Top_Bottom; 953371
J3: JTAG; PinHeader_2x06_P1.27mm_Vertical_SMD
JP1, JP2: Jumper_3_Open; SolderJumper-3_P1.3mm_Open_Pad1.0x1.5mm_NumberLabels
L1: L_Small; L_Bourns-SRN6028
Q1: Q_PMOS_GDS; TO-252-2
Q2, Q3, Q4: MBT3904DW1T1G; SOT-363_SC-70-6
R1, R2, R4, R5: R_Small; R_0603_1608Metric
R3: 120,DNP; R_0805_2012Metric
R6, R7, R9, R11: 240R; R_0603_1608Metric
R8, R14: 10k; R_0603_1608Metric
R10, R15, R16, R17, R24, R25, R26: 10k; R_0402_1005Metric
R12, R13: 100k; R_0402_1005Metric
R18, R19, R20, R27, R29, R30: 1k; R_0402_1005Metric
R21, R22, R23, R28, R31, R32: 499R; R_0402_1005Metric
SW1: SW_Push; SW_RS-032G05A3-SMRT
TP1: VOUT; TestPoint_2Pads_Pitch2.54mm_Drill0.8mm
U1: TPS5430DDA; TI_SO-PowerPAD-8_ThermalVias
U2: SN65HVD230; SOIC-8_3.9x4.9mm_P1.27mm
U3: STM32F103C8T6; LQFP-48_7x7mm_P0.5mm
U4: DRV8844PWP; HTSSOP-28-1EP_4.4x9.7mm_P0.65mm_EP2.85x5.4mm_ThermalVias
Y1: 12mhz; Crystal_SMD_3225-4Pin_3.2x2.5mm

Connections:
+3V3: C4.1, C5.1, C6.2, C7.2, C8.2, C9.2, C10.2, C11.2, D3.2 (A), D4.2 (A), D5.2 (A), D6.2 (A), JP1.1 (A), JP2.1 (A), L1.2, R4.1, R10.2, TP1.2, U2.3 (VCC), U3.1 (VBAT), U3.9 (VDDA), U3.24 (VDD), U3.36 (VDD), U3.48 (VDD)
+12V: D1.2 (A), J2.1
/12VOUT: C15.2, C16.1, C17.1, Q1.2 (D), U4.4 (VM-1), U4.11 (VM)
/BOOT: C3.1, U1.1 (BOOT)
/BOOT0: R12.2, U3.44 (BOOT0)
/BOOT1: R13.2, U3.19 (PB1)
/CANH: D7.2 (A2), J2.16, R3.1, U2.7 (CANH)
/CANL: D7.1 (A1), J2.8, R3.2, U2.6 (CANL)
/CANRX: U2.4 (R), U3.45 (PB8)
/CANTX: U2.1 (D), U3.46 (PB9)
/CP1: C14.1, U4.1 (CP1)
/CP2: C14.2, U4.2 (CP2)
/DRV_NRESET: R8.2, U4.16 (NRESET)
/EN1: U3.14 (PA4), U4.26 (EN1)
/EN2: U3.16 (PA6), U4.24 (EN2)
/EN3: U3.20 (PB2), U4.22 (EN3)
/EN4: U3.22 (PB11), U4.20 (EN4)
/FUSED_VBAT_IN: F1.2, Q1.3 (S), R14.2
/GPI1: J2.12, R24.1
/GPIO_GPI1: Q2.3 (C2), U3.29 (PA8)
/GPIO_GPI2: Q2.6 (C1), U3.30 (PA9)
/GPIO_GPI3: Q3.3 (C2), U3.31 (PA10)
/GPIO_GPI4: Q3.6 (C1), U3.32 (PA11)
/GPIO_GPI5: Q4.3 (C2), U3.27 (PB14)
/GPIO_VOUT_EN: Q4.6 (C1), U3.28 (PB15)
/IN1: U3.13 (PA3), U4.27 (IN1)
/IN2: U3.15 (PA5), U4.25 (IN2)
/IN3: U3.17 (PA7), U4.23 (IN3)
/IN4: U3.21 (PB10), U4.21 (IN4)
/JTCK: J3.1 (TCK), U3.37 (PA14)
/JTDI: J3.9 (TDI), U3.38 (PA15)
/JTDO: J3.3 (TDO), U3.39 (PB3)
/JTMS: J3.5 (TMS), U3.34 (PA13)
/MOTOR1_OUT1: J2.4, U4.5 (OUTPUT1)
/MOTOR1_OUT2: J2.5, U4.7 (OUTPUT2)
/MOTOR2_OUT1: J2.6, U4.8 (OUTPUT3)
/MOTOR2_OUT2: J2.7, U4.10 (OUTPUT4)
/NFAULT: R7.2, U3.25 (PB12), U4.18 (NFAULT)
/NRST: C18.2, SW1.1, U3.7 (NRST)
/NSLEEP: U3.26 (PB13), U4.17 (NSLEEP)
/OSC_IN: C12.1, U3.5 (PD0), Y1.1
/OSC_OUT: C13.1, U3.6 (PD1), Y1.3
/PB0: R9.2, U3.18 (PB0)
/PH: C3.2, D2.1 (K), L1.1, U1.8 (PH)
/V3P3OUT: C19.1, R8.1, U4.15 (V3P3OUT)
/VBATT_SENSE: R1.2, R2.1, U3.10 (PA0)
/VBAT_IN: F1.1, J2.2, J2.3
/VCP: C15.1, U4.3 (VCP)
/VIN: C1.1, C2.1, D1.1 (K), R1.1, U1.7 (VIN)
/VOUT_EN: Q1.1 (G), R14.1, R17.1
/VSENSE: R4.2, R5.1, U1.4 (VSENSE)
GND: C1.2, C2.2, C4.2, C5.2, C6.1, C7.1, C8.1, C9.1, C10.1, C11.1, C12.2, C13.2, C16.2, C17.2, C19.2, D2.2 (A), D7.3 (common), H1.1, H2.1, J3.2 (GND), J3.10 (GND), JP1.3 (B), JP2.3 (B), Q2.1 (E1), Q2.4 (E2), Q3.1 (E1), Q3.4 (E2), Q4.1 (E1), Q4.4 (E2), R2.2, R5.2, R6.2, R11.2, R21.2, R22.2, R23.2, R28.2, R31.2, R32.2, TP1.1, U1.6 (GND), U1.9 (GNDPAD), U2.2 (GND), U2.8 (Rs), U3.8 (VSSA), U3.23 (VSS), U3.35 (VSS), U3.47 (VSS), U4.6 (SRC12), U4.9 (SRC34), U4.14 (VNEG-2), U4.19 (LGND), U4.28 (VNEG), U4.29 (VNEG), Y1.2, Y1.4
unnamed: C18.1, R10.1, SW1.2
unnamed: D3.1 (K), R6.1
unnamed: D4.1 (K), R7.1
unnamed: D5.1 (K), R9.1
unnamed: D6.1 (K), R11.1
unnamed: JP1.2 (C), R12.1
unnamed: JP2.2 (C), R13.1
unnamed: Q2.2 (B1), R15.2, R18.1
unnamed: Q2.5 (B2), R24.2, R27.1
unnamed: Q3.2 (B1), R16.2, R19.1
unnamed: Q3.5 (B2), R25.2, R29.1
unnamed: Q4.2 (B1), R17.2, R20.1
unnamed: Q4.5 (B2), R26.2, R30.1
unnamed: R18.2, R21.1
unnamed: R19.2, R22.1
unnamed: R20.2, R23.1
unnamed: R27.2, R28.1
unnamed: R29.2, R31.1
unnamed: R30.2, R32.1

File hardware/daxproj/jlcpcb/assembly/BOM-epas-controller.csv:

Comment,Designator,Footprint,LCSC
12mhz,Y1,Crystal_SMD_3225-4Pin_3.2x2.5mm,C9002
TPS5430DDA,U1,TI_SO-PowerPAD-8_ThermalVias,C9864
STM32F103C8T6,U3,LQFP-48_7x7mm_P0.5mm,STM32F103C8T6
100nf,C11,C_0402_1005Metric,
C_Small,C12,C_0402_1005Metric,
AVR-JTAG-10,J2,PinHeader_2x06_P1.27mm_Vertical_SMD,
100nf,C5,C_0402_1005Metric,
100nf,C7,C_0402_1005Metric,
C_Small,C4,C_0805_2012Metric,
100nf,C9,C_0402_1005Metric,
C_Small,C3,C_0805_2012Metric,
10k,R7,R_0402_1005Metric,
RED,D4,LED_0603_1608Metric,
L_Small,L1,L_Bourns-SRN6028,
"120,DNP",R3,R_0805_2012Metric,
100nf,C10,C_0402_1005Metric,
100nf,C8,C_0402_1005Metric,
R_Small,R2,R_0603_1608Metric,
MountingHole_Pad,H1,MountingHole_3.2mm_M3_Pad_Via,
Jumper_3_Open,JP1,SolderJumper-3_P1.3mm_Open_Pad1.0x1.5mm_NumberLabels,
240R,R6,R_0603_1608Metric,
D_Small,D2,D_SOD-123F,
VOUT,TP1,TestPoint_2Pads_Pitch2.54mm_Drill0.8mm,
240R,R8,R_0603_1608Metric,
R_Small,R1,R_0603_1608Metric,
1565749-3,J1,1565749-3,
SW_Push,SW1,SW_RS-032G05A3-SMRT,
Jumper_3_Open,JP2,SolderJumper-3_P1.3mm_Open_Pad1.0x1.5mm_NumberLabels,
GRN,D3,LED_0603_1608Metric,
10uf,C1,C_0805_2012Metric,
C_Small,C13,C_0402_1005Metric,
TPSMA6L78A,D1,D_SMA,
4.7nf,C6,C_0805_2012Metric,
MountingHole_Pad,H2,MountingHole_3.2mm_M3_Pad_Via,
100k,R10,R_0402_1005Metric,
R_Small,R4,R_0603_1608Metric,
100k,R9,R_0402_1005Metric,
1uf,C2,C_0805_2012Metric,
R_Small,R5,R_0603_1608Metric,
SN65HVD230,U2,SOIC-8_3.9x4.9mm_P1.27mm,
100nf,C14,C_0402_1005Metric,
